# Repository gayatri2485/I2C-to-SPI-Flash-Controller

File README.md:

# I2C-to-SPI-Flash-Controller
Design of an I2C-to-SPI Flash Memory Controller using SC18IS606 and W25Q32JV, including schematic design, PCB layout and power supply analysis.

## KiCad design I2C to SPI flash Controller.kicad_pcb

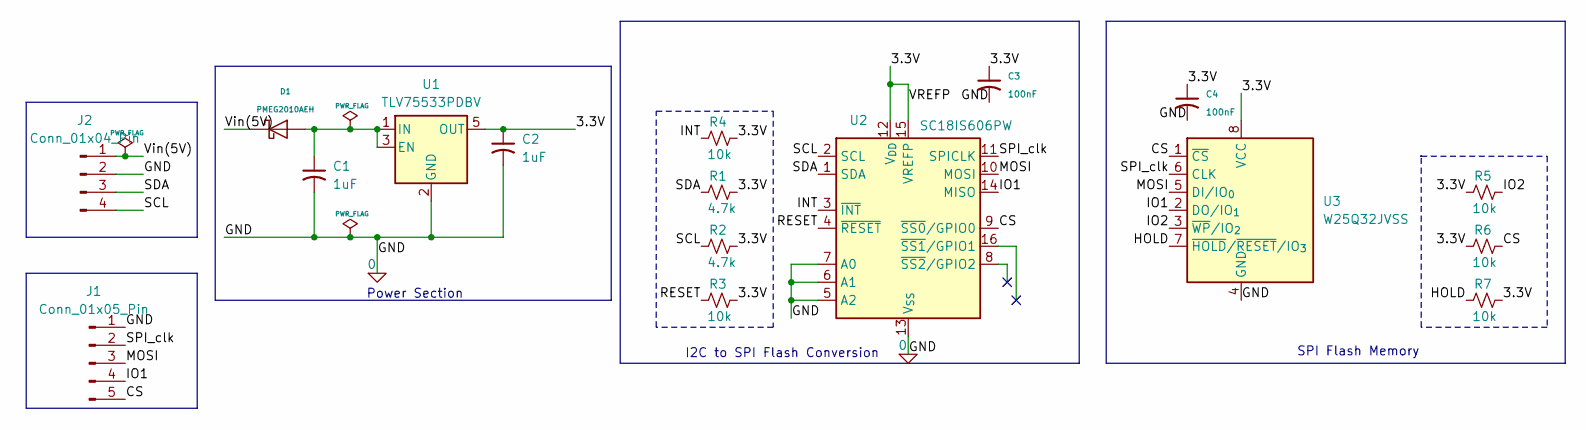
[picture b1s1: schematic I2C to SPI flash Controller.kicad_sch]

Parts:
C1, C2: 1uF; C_0603_1608Metric
C3, C4: 100nF; C_0603_1608Metric
D1: PMEG2010AEH; D_SOD-123F
J1: Conn_01x05_Pin; PinHeader_1x05_P2.54mm_Vertical
J2: Conn_01x04_Pin; PinHeader_1x04_P2.54mm_Vertical
R1, R2: 4.7k; R_0603_1608Metric
R3, R4, R5, R6, R7: 10k; R_0603_1608Metric
U1: TLV75533PDBV; SOT-23-5
U2: SC18IS606PW; TSSOP-16_4.4x5mm_P0.65mm
U3: W25Q32JVSS; SOIC-8_5.3x5.3mm_P1.27mm

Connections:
0: C1.2, C2.2, C3.2, C4.2, J1.1, J2.2, U1.2 (GND), U2.5 (A2), U2.6 (A1), U2.7 (A0), U2.13 (V_{SS}), U3.4 (GND)
/3.3V: C2.1, C3.1, C4.1, R1.1, R2.1, R3.1, R4.1, R5.2, R6.2, R7.1, U1.5 (OUT), U2.12 (V_{DD}), U2.15 (VREFP), U3.8 (VCC)
/CS: J1.5, R6.1, U2.9 (~SS0/GPIO0), U3.1 (~CS)
/HOLD: R7.2, U3.7 (~HOLD/~RESET/IO_{3})
/INT: R4.2, U2.3 (~INT)
/IO1: J1.4, U2.14 (MISO), U3.2 (DO/IO_{1})
/IO2: R5.1, U3.3 (~WP/IO_{2})
/MOSI: J1.3, U2.10 (MOSI), U3.5 (DI/IO_{0})
/RESET: R3.2, U2.4 (~RESET)
/SCL: J2.4, R2.2, U2.2 (SCL)
/SDA: J2.3, R1.2, U2.1 (SDA)
/SPI_clk: J1.2, U2.11 (SPICLK), U3.6 (CLK)
/Vin(5V): D1.1 (K), J2.1
unnamed: C1.1, D1.2 (A), U1.1 (IN), U1.3 (EN)

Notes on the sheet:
I2C to SPI Flash Conversion
Power Section
SPI Flash Memory

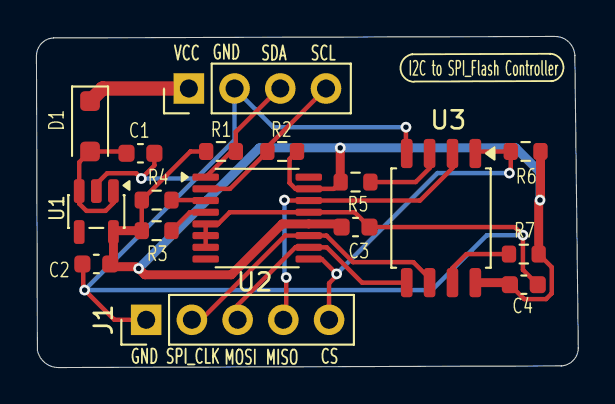
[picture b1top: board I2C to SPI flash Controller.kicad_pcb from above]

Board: 2 copper layers, 30.1 x 18.4 mm, 17 parts (0 on the bottom side), 14 nets.
